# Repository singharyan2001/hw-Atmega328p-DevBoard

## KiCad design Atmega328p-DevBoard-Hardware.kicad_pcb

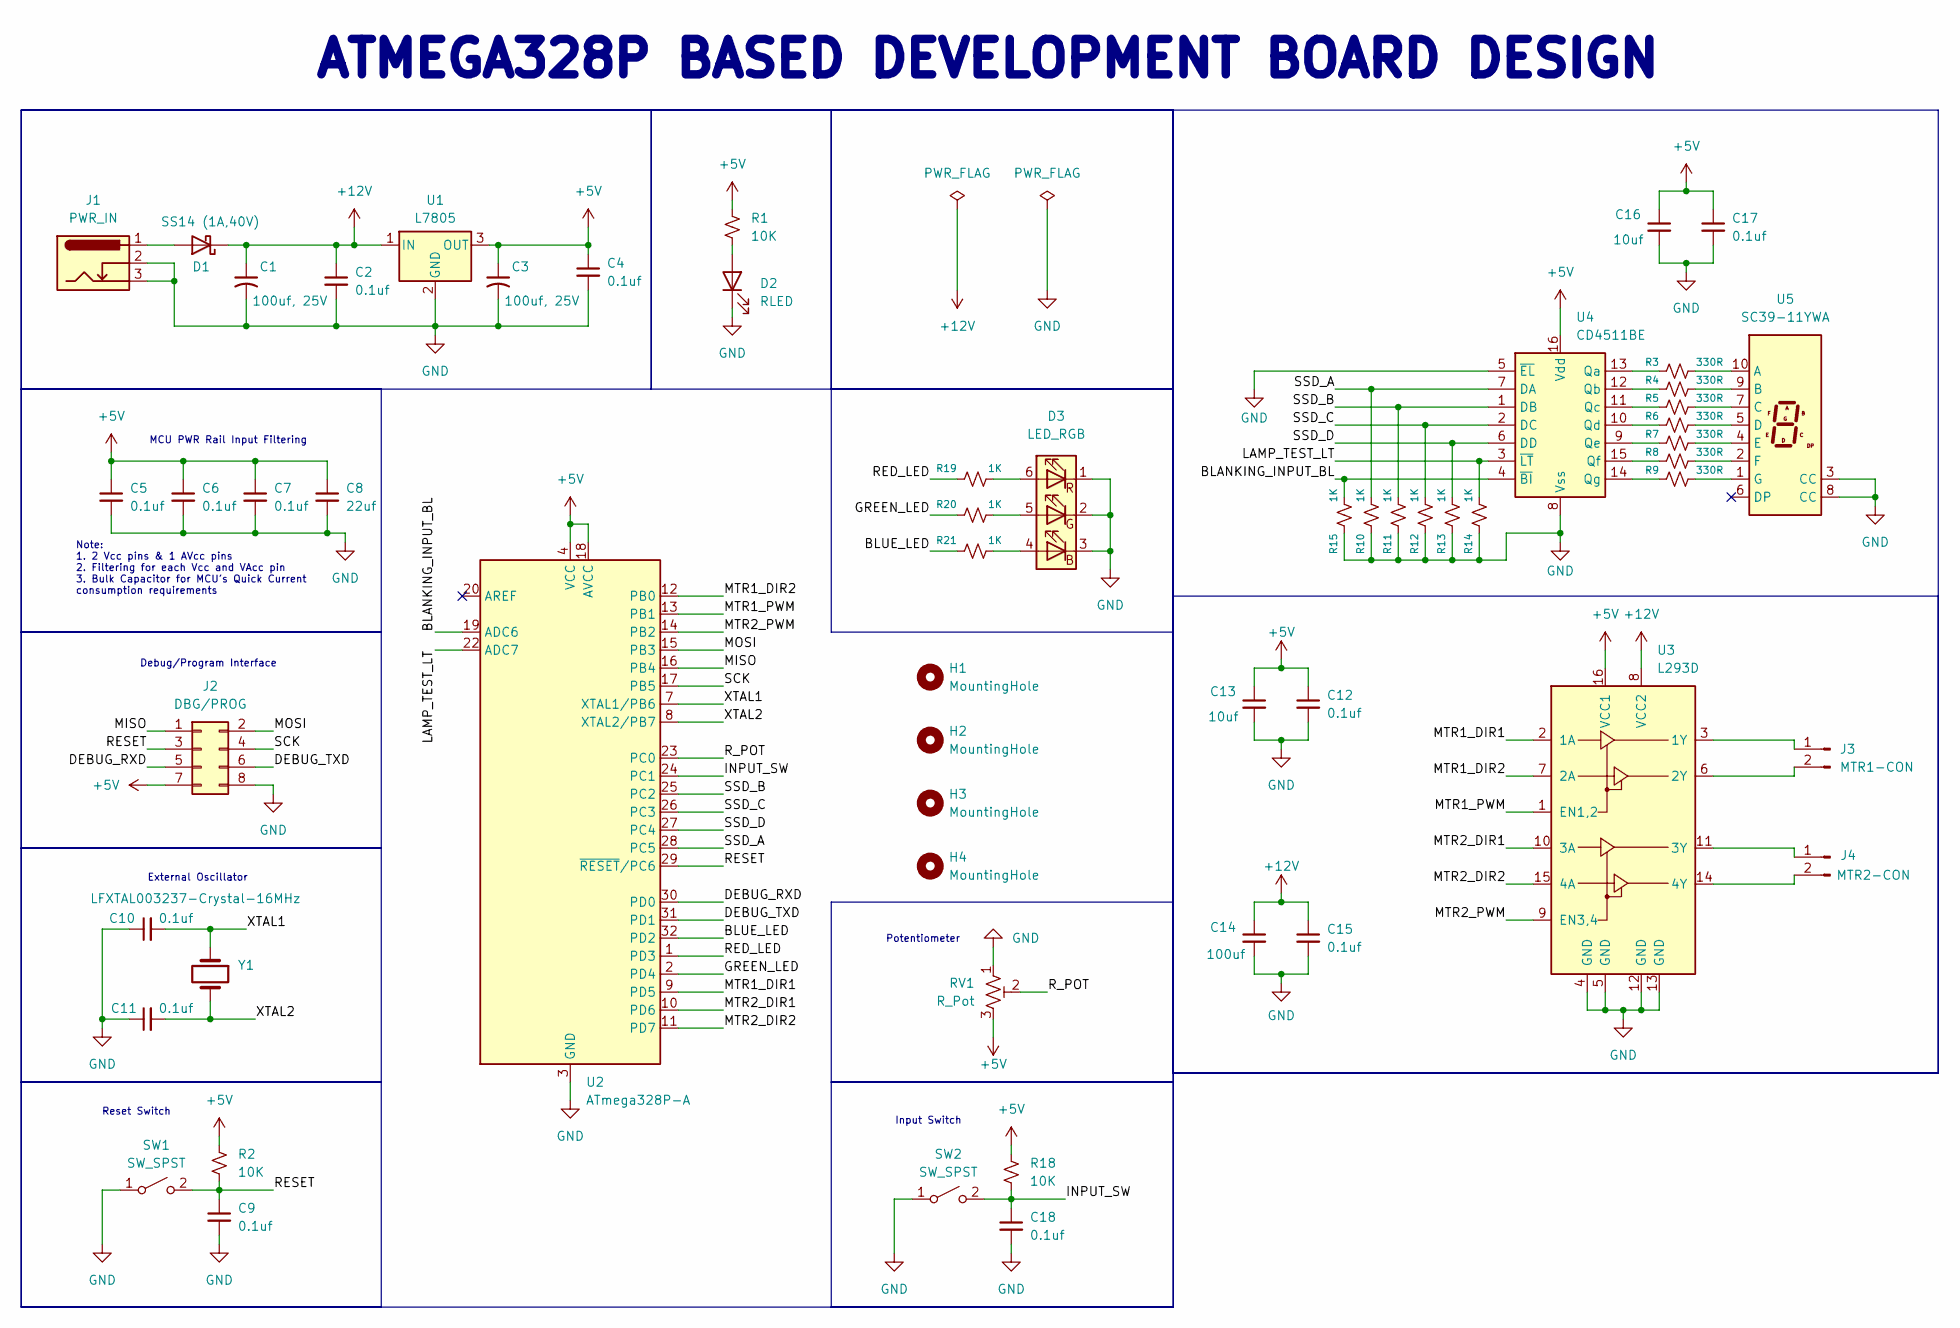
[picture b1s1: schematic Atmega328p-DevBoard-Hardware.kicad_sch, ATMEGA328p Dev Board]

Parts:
C1, C3: 100uf, 25V; C_Elec_6.3x7.7
C2, C4, C5, C6, C7, C9, C10, C11, C12, C15, C17, C18: 0.1uf; C_0805_2012Metric_Pad1.18x1.45mm_HandSolder
C8: 22uf; C_0805_2012Metric_Pad1.18x1.45mm_HandSolder
C13, C16: 10uf; C_0805_2012Metric_Pad1.18x1.45mm_HandSolder
C14: 100uf; C_0805_2012Metric_Pad1.18x1.45mm_HandSolder
D1: SS14 (1A,40V); D_SMA_Handsoldering
D2: RLED; LED_0805_2012Metric_Pad1.15x1.40mm_HandSolder
D3: LED_RGB; LED_RGB_5050-6
H1, H2, H3, H4: MountingHole; MountingHole_3.2mm_M3_DIN965
J1: PWR_IN; BarrelJack_Horizontal
J2: DBG/PROG; PinHeader_2x04_P2.54mm_Vertical
J3: MTR1-CON; PhoenixContact_MC_1,5_2-G-3.81_1x02_P3.81mm_Horizontal
J4: MTR2-CON; PhoenixContact_MC_1,5_2-G-3.81_1x02_P3.81mm_Horizontal
R1, R2, R18: 10K; R_0805_2012Metric_Pad1.20x1.40mm_HandSolder
R3, R4, R5, R6, R7, R8, R9: 330R; R_0805_2012Metric_Pad1.20x1.40mm_HandSolder
R10, R11, R12, R13, R14, R15, R19, R20, R21: 1K; R_0805_2012Metric_Pad1.20x1.40mm_HandSolder
RV1: R_Pot; Potentiometer_Bourns_3296W_Vertical
SW1, SW2: SW_SPST; SW_Tactile_SPST_NO_Straight_CK_PTS636Sx25SMTRLFS
U1: L7805; TO-252-2
U2: ATmega328P-A; TQFP-32_7x7mm_P0.8mm
U3: L293D; DIP-16_W7.62mm
U4: CD4511BE; DIP-16_W7.62mm_LongPads
U5: SC39-11YWA; Sx39-1xxxxx
Y1: LFXTAL003237-Crystal-16MHz; Crystal_SMD_HC49-SD

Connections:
+5V: C3.1, C4.1, C5.1, C6.1, C7.1, C8.1, C12.1, C13.1, C16.1, C17.1, J2.7, R1.1, R2.1, R18.1, RV1.3, U1.3 (OUT), U2.4 (VCC), U2.6 (VCC), U2.18 (AVCC), U3.16 (VCC1), U4.16 (Vdd)
+12V: C1.1, C2.1, C14.1, C15.1, D1.1 (K), U1.1 (IN), U3.8 (VCC2)
/BLANKING_INPUT_BL: R15.2, U2.19 (ADC6), U4.4 (~BI)
/BLUE_LED: R21.1, U2.32 (PD2)
/DEBUG_RXD: J2.5, U2.30 (PD0)
/DEBUG_TXD: J2.6, U2.31 (PD1)
/GREEN_LED: R20.1, U2.2 (PD4)
/INPUT_SW: C18.1, R18.2, SW2.2 (B), U2.24 (PC1)
/LAMP_TEST_LT: R14.2, U2.22 (ADC7), U4.3 (~LT)
/MISO: J2.1, U2.16 (PB4)
/MOSI: J2.2, U2.15 (PB3)
/MTR1_DIR1: U2.9 (PD5), U3.2 (1A)
/MTR1_DIR2: U2.12 (PB0), U3.7 (2A)
/MTR1_PWM: U2.13 (PB1), U3.1 (EN1,2)
/MTR2_DIR1: U2.10 (PD6), U3.10 (3A)
/MTR2_DIR2: U2.11 (PD7), U3.15 (4A)
/MTR2_PWM: U2.14 (PB2), U3.9 (EN3,4)
/RED_LED: R19.1, U2.1 (PD3)
/RESET: C9.1, J2.3, R2.2, SW1.2 (B), U2.29 (~RESET/PC6)
/R_POT: RV1.2, U2.23 (PC0)
/SCK: J2.4, U2.17 (PB5)
/SSD_A: R10.2, U2.28 (PC5), U4.7 (DA)
/SSD_B: R11.2, U2.25 (PC2), U4.1 (DB)
/SSD_C: R12.2, U2.26 (PC3), U4.2 (DC)
/SSD_D: R13.2, U2.27 (PC4), U4.6 (DD)
/XTAL1: C10.2, U2.7 (XTAL1/PB6), Y1.1
/XTAL2: C11.2, U2.8 (XTAL2/PB7), Y1.2
GND: C1.2, C2.2, C3.2, C4.2, C5.2, C6.2, C7.2, C8.2, C9.2, C10.1, C11.1, C12.2, C13.2, C14.2, C15.2, C16.2, C17.2, C18.2, D2.1 (K), D3.1 (RK), D3.2 (GK), D3.3 (BK), J1.2, J1.3, J2.8, R10.1, R11.1, R12.1, R13.1, R14.1, R15.1, RV1.1, SW1.1 (A), SW2.1 (A), U1.2 (GND), U2.3 (GND), U2.5 (GND), U2.21 (GND), U3.4 (GND), U3.5 (GND), U3.12 (GND), U3.13 (GND), U4.5 (~EL), U4.8 (Vss), U5.3 (CC), U5.8 (CC)
unnamed: D1.2 (A), J1.1
unnamed: D2.2 (A), R1.2
unnamed: D3.4 (BA), R21.2
unnamed: D3.5 (GA), R20.2
unnamed: D3.6 (RA), R19.2
unnamed: J3.1, U3.3 (1Y)
unnamed: J3.2, U3.6 (2Y)
unnamed: J4.1, U3.11 (3Y)
unnamed: J4.2, U3.14 (4Y)
unnamed: R3.1, U4.13 (Qa)
unnamed: R4.1, U4.12 (Qb)
unnamed: R5.1, U4.11 (Qc)
unnamed: R6.1, U4.10 (Qd)
unnamed: R7.1, U4.9 (Qe)
unnamed: R8.1, U4.15 (Qf)
unnamed: R9.1, U4.14 (Qg)
unnamed: R3.2, U5.10 (A)
unnamed: R4.2, U5.9 (B)
unnamed: R5.2, U5.7 (C)
unnamed: R6.2, U5.5 (D)
unnamed: R7.2, U5.4 (E)
unnamed: R8.2, U5.2 (F)
unnamed: R9.2, U5.1 (G)

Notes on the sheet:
External Oscillator
Debug/Program Interface
Potentiometer
MCU PWR Rail Input Filtering
Note: 1. 2 Vcc pins & 1 AVcc pins 2. Filtering for each Vcc and VAcc pin 3. Bulk Capacitor for MCU's Quick Current consumption requirements
ATMEGA328P BASED DEVELOPMENT BOARD DESIGN
Input Switch
Reset Switch

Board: 2 copper layers, 57 parts (0 on the bottom side), 51 nets, no tracks yet.

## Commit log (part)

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2026-06-09 init commit
2026-06-10 updated documentation - new topics notes added
2026-06-11 added capacitor section in documentation file
2026-06-11 Updated documentation - Section 1 Completed, Section 2 in-progress
2026-06-13 updated documentation: Module 1 completed, module 2 in-progress, current in power supply design stage
2026-06-15 power supply design section - diode selection, input & output filtering capacitor design section completed, final led design section in-progress
2026-06-15 completed power supply design section with schematics, now working on MCU Section
2026-06-17 finished motor driver design section in docs and schematics
